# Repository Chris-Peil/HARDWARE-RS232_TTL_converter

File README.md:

# HARDWARE-RS232_TTL_converter
DB9 sized PCB for RS232 to TTL

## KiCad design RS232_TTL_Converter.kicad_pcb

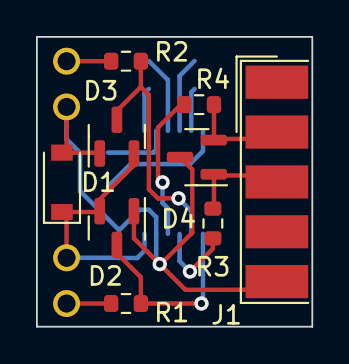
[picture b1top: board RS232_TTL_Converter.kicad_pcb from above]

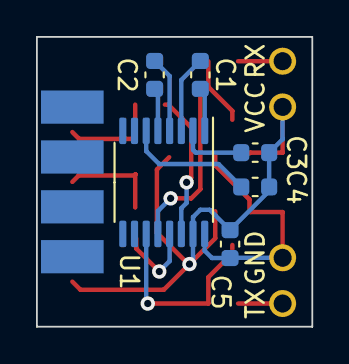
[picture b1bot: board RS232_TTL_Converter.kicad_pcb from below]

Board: 2 copper layers, 15.3 x 16.1 mm, 19 parts (6 on the bottom side), 16 nets.

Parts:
C1, C5: 0.1uF; C_0603_1608Metric
C2, C3, C4: 0.47uF; C_0603_1608Metric
D1: MBR0520; D_SOD-123
D2, D3: BAT54S; SOT-23
D4: SM712_SOT23; SOT-23
GND: MountingHole_Pad; Through_Hole_Pad_1.5mm
J1: DB9_Female; DSUB-9_Female_EdgeMount_P2.77mm
R1, R2, R3, R4: 330R; R_0603_1608Metric
RX: MountingHole_Pad; Through_Hole_Pad_1.5mm
TX: MountingHole_Pad; Through_Hole_Pad_1.5mm
U1: MAX3232; TSSOP-16_4.4x5mm_P0.65mm
VCC: MountingHole_Pad; Through_Hole_Pad_1.5mm

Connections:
/RX: R2.1, RX.1
/TX: R1.1, TX.1
Device RX: D3.3, R2.2, U1.12 (R1OUT)
Device TX: D2.3, R1.2, U1.11 (T1IN)
GND: C3.2, C4.2, C5.1, D1.2 (A), D2.1, D3.1, D4.3 (common), J1.5, U1.15 (GND), VCC.1
Host RX: R4.1, U1.14 (T1OUT)
Host TX: R3.1, U1.13 (R1IN)
unnamed: C1.1, U1.1 (C1+)
unnamed: C1.2, U1.3 (C1-)
unnamed: C2.1, U1.4 (C2+)
unnamed: C2.2, U1.5 (C2-)
unnamed: C3.1, U1.2 (VS+)
unnamed: C4.1, U1.6 (VS-)
unnamed: D4.1 (A1), J1.3, R3.2
unnamed: D4.2 (A2), J1.2, R4.2
VCC: C5.2, D1.1 (K), D2.2, D3.2, GND.1, U1.16 (VCC)

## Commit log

2025-11-27 finalised draft
2025-11-27 added BOM, need to check PCB thickness
2025-11-28 changed pcb thickness to 1.2mm
